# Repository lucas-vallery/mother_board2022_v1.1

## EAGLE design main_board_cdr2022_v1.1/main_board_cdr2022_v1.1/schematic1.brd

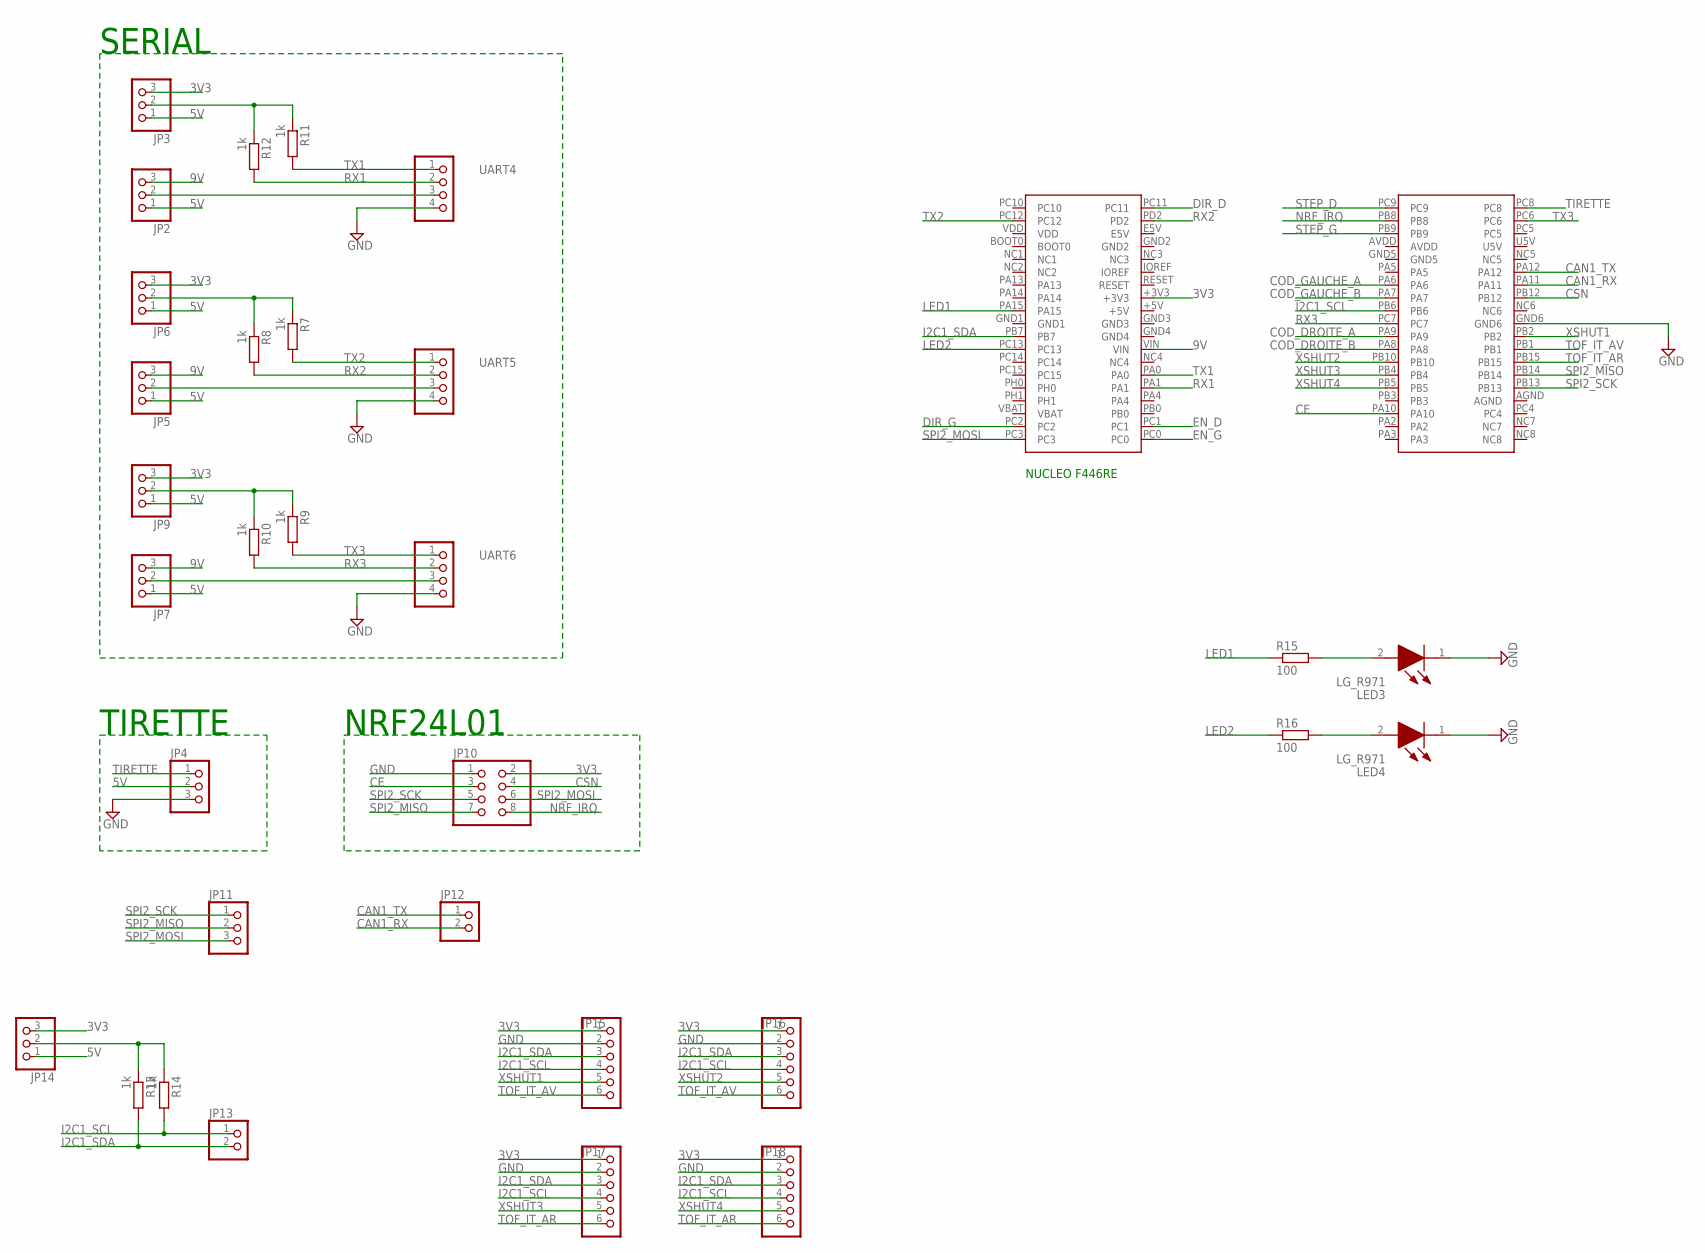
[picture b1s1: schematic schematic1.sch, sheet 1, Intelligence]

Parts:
JP2, JP3, JP4, JP5, JP6, JP7, JP9, JP11, JP14: PINHD-1X3; 1X03
JP10: PINHD-2X4; 2X04
JP12, JP13: PINHD-1X2; 1X02
JP15, JP16, JP17, JP18: PINHD-1X6; 1X06
LED3, LED4: LG_R971; LEDC2012X90N
R7, R8, R9, R10, R11, R12, R13, R14: 1k; R0805
R15, R16: 100; R0805
U$1: NUCLEO_F446RE; MB1136
UART4, UART5, UART6: PINHD-1X4; 1X04

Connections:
3V3: JP3.3, JP6.3, JP9.3, JP10.2, JP14.3, JP15.1, JP16.1, JP17.1, JP18.1, U$1.+3V3
5V: JP2.1, JP3.1, JP4.2, JP5.1, JP6.1, JP7.1, JP9.1, JP14.1; also elsewhere on the board
9V: JP2.3, JP5.3, JP7.3, U$1.VIN; also elsewhere on the board
CAN1_RX: JP12.2, U$1.PA11
CAN1_TX: JP12.1, U$1.PA12
CE: JP10.3, U$1.PA10
COD_DROITE_A: U$1.PA9; also elsewhere on the board
COD_DROITE_B: U$1.PA8; also elsewhere on the board
COD_GAUCHE_A: U$1.PA6; also elsewhere on the board
COD_GAUCHE_B: U$1.PA7; also elsewhere on the board
CSN: JP10.4, U$1.PB12
DIR_D: U$1.PC11; also elsewhere on the board
DIR_G: U$1.PC2; also elsewhere on the board
EN_D: U$1.PC1; also elsewhere on the board
EN_G: U$1.PC0; also elsewhere on the board
GND: JP4.3, JP10.1, JP15.2, JP16.2, JP17.2, JP18.2, LED3.1 (K), LED4.1 (K), U$1.GND6, UART4.4, UART5.4, UART6.4; also elsewhere on the board
I2C1_SCL: JP13.1, JP15.4, JP16.4, JP17.4, JP18.4, R14.2, U$1.PB6
I2C1_SDA: JP13.2, JP15.3, JP16.3, JP17.3, JP18.3, R13.2, U$1.PB7
LED1: R15.1, U$1.PA15
LED2: R16.1, U$1.PC13
unnamed: JP3.2, R11.1, R12.1
unnamed: JP6.2, R7.1, R8.1
unnamed: JP9.2, R9.1, R10.1
unnamed: LED3.2 (A), R15.2
unnamed: JP14.2, R13.1, R14.1
unnamed: LED4.2 (A), R16.2
NRF_IRQ: JP10.8, U$1.PB8
RX1: R12.2, U$1.PA1, UART4.2
RX2: R8.2, U$1.PD2, UART5.2
RX3: R10.2, U$1.PC7, UART6.2
SPI2_MISO: JP10.7, JP11.2, U$1.PB14
SPI2_MOSI: JP10.6, JP11.3, U$1.PC3
SPI2_SCK: JP10.5, JP11.1, U$1.PB13
STEP_D: U$1.PC9; also elsewhere on the board
STEP_G: U$1.PB9; also elsewhere on the board
TIRETTE: JP4.1, U$1.PC8
TOF_IT_AR: JP17.6, JP18.6, U$1.PB15
TOF_IT_AV: JP15.6, JP16.6, U$1.PB1
TX1: R11.2, U$1.PA0, UART4.1
TX2: R7.2, U$1.PC12, UART5.1
TX3: R9.2, U$1.PC6, UART6.1
VIN: JP2.2, UART4.3
VIN1: JP5.2, UART5.3
VIN2: JP7.2, UART6.3
XSHUT1: JP15.5, U$1.PB2
XSHUT2: JP16.5, U$1.PB10
XSHUT3: JP17.5, U$1.PB4
XSHUT4: JP18.5, U$1.PB5

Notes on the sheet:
NUCLEO F446RE
SERIAL
TIRETTE
NRF24L01

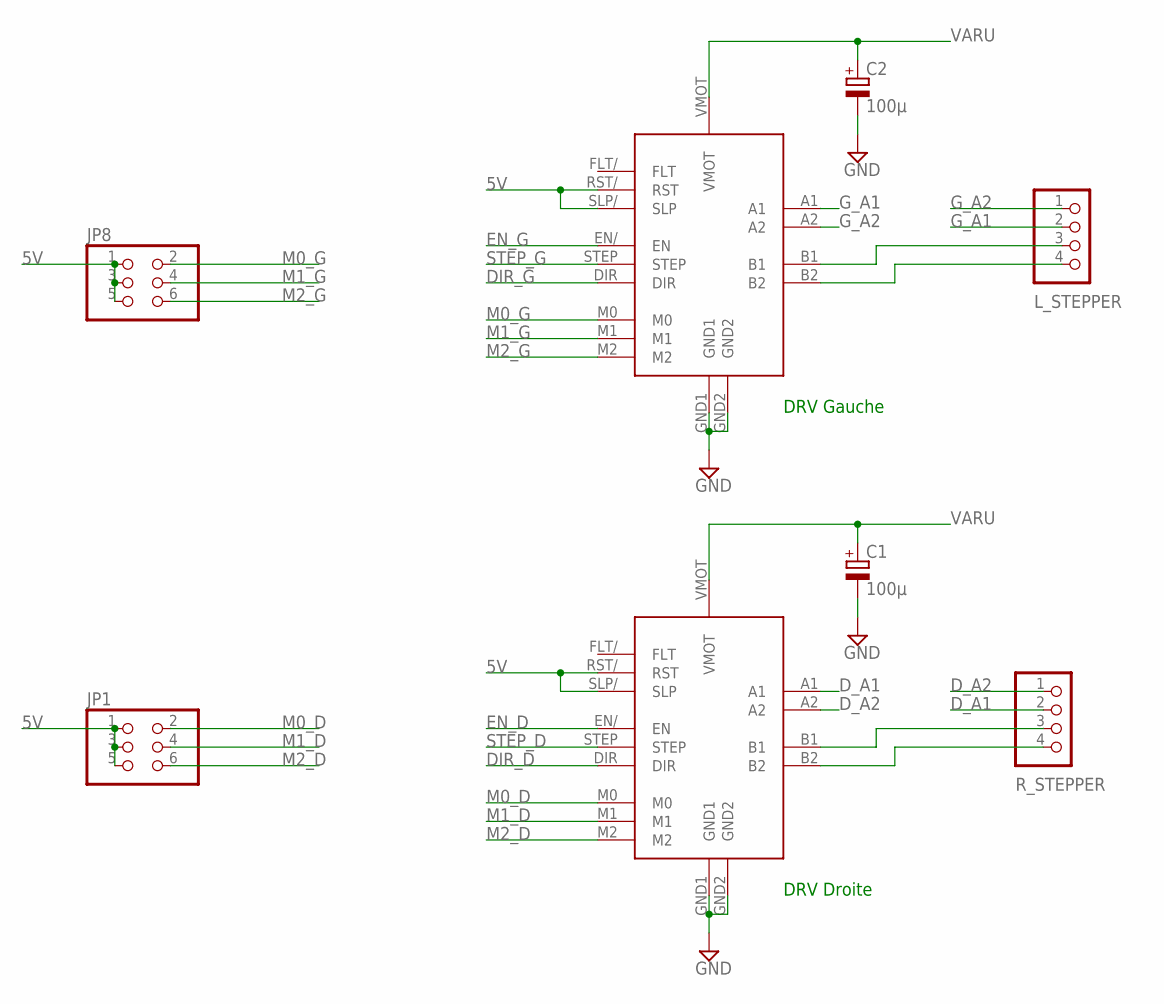
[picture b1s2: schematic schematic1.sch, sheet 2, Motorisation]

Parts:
C1, C2: 100µ; E5-6
JP1, JP8: PINHD-2X3; 2X03
L_STEPPER: PINHD-1X4; 1X04
R_STEPPER: PINHD-1X4; 1X04
U$2, U$3: POLOLU_DRV8825

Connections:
5V: JP1.1, JP1.3, JP1.5, JP8.1, JP8.3, JP8.5, U$2.RST/ (RST), U$2.SLP/ (SLP), U$3.RST/ (RST), U$3.SLP/ (SLP); also elsewhere on the board
DIR_D: U$3.DIR; also elsewhere on the board
DIR_G: U$2.DIR; also elsewhere on the board
D_A1: R_STEPPER.2, U$3.A1
D_A2: R_STEPPER.1, U$3.A2
EN_D: U$3.EN/ (EN); also elsewhere on the board
EN_G: U$2.EN/ (EN); also elsewhere on the board
GND: C1.-, C2.-, U$2.GND1, U$2.GND2, U$3.GND1, U$3.GND2; also elsewhere on the board
G_A1: L_STEPPER.2, U$2.A1
G_A2: L_STEPPER.1, U$2.A2
M0_D: JP1.2, U$3.M0
M0_G: JP8.2, U$2.M0
M1_D: JP1.4, U$3.M1
M1_G: JP8.4, U$2.M1
M2_D: JP1.6, U$3.M2
M2_G: JP8.6, U$2.M2
unnamed: L_STEPPER.3, U$2.B1
unnamed: L_STEPPER.4, U$2.B2
unnamed: R_STEPPER.3, U$3.B1
unnamed: R_STEPPER.4, U$3.B2
STEP_D: U$3.STEP; also elsewhere on the board
STEP_G: U$2.STEP; also elsewhere on the board
VARU: C1.+, C2.+, U$2.VMOT, U$3.VMOT; also elsewhere on the board

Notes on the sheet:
DRV Gauche
DRV Droite

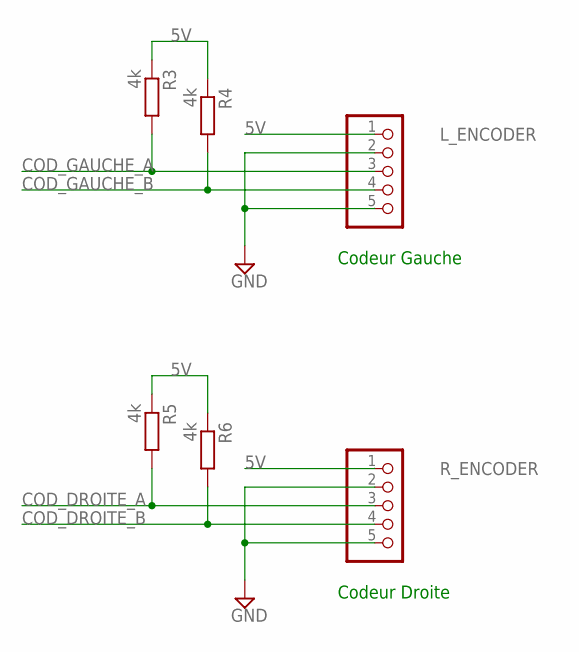
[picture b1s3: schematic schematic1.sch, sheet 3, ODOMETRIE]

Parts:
L_ENCODER: PINHD-1X5; 1X05
R3, R4, R5, R6: 4k; R0805
R_ENCODER: PINHD-1X5; 1X05

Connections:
5V: L_ENCODER.1, R3.1, R4.1, R5.1, R6.1, R_ENCODER.1; also elsewhere on the board
COD_DROITE_A: R5.2, R_ENCODER.3; also elsewhere on the board
COD_DROITE_B: R6.2, R_ENCODER.4; also elsewhere on the board
COD_GAUCHE_A: L_ENCODER.3, R3.2; also elsewhere on the board
COD_GAUCHE_B: L_ENCODER.4, R4.2; also elsewhere on the board
GND: L_ENCODER.2, L_ENCODER.5, R_ENCODER.2, R_ENCODER.5; also elsewhere on the board

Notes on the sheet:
Codeur Gauche
Codeur Droite

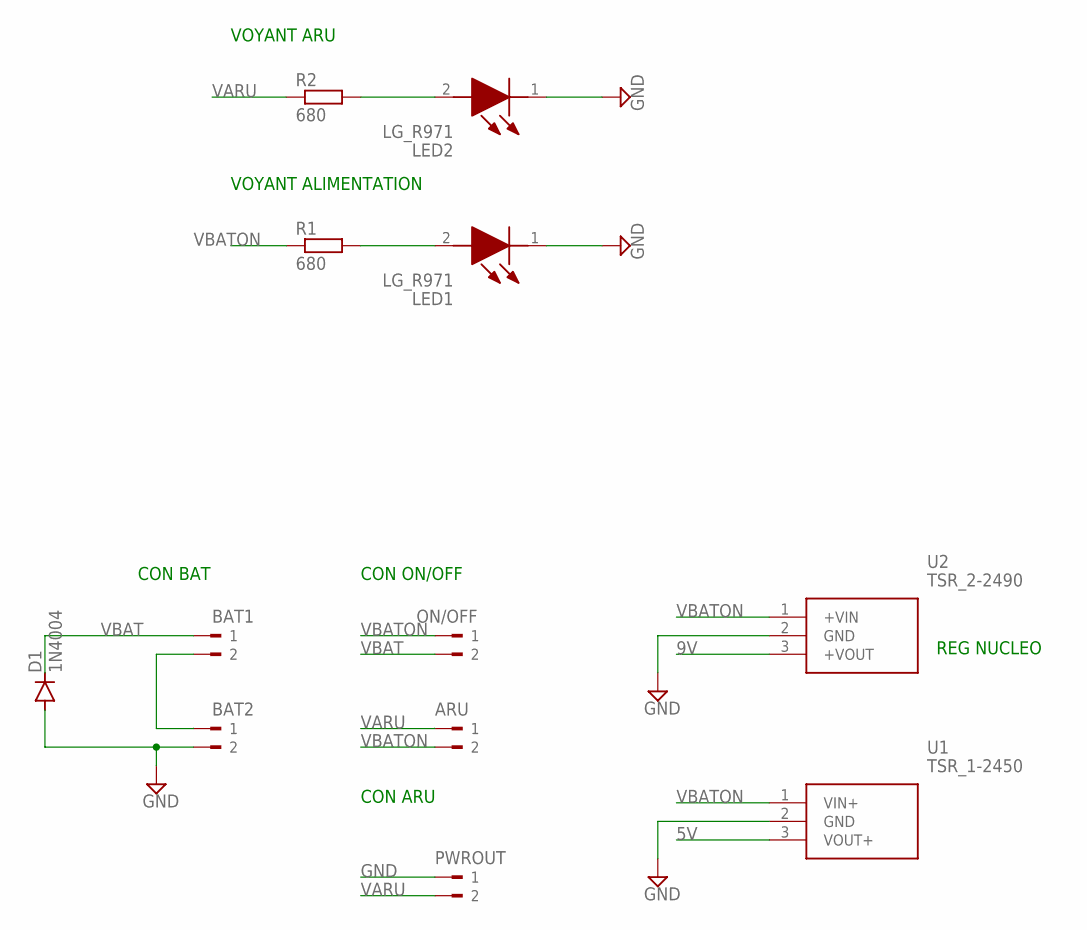
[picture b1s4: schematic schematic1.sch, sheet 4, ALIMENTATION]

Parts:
ARU: 180G-2
BAT1, BAT2: 180G-2
D1: 1N4004; DO41-10
LED1, LED2: LG_R971; LEDC2012X90N
ON/OFF: 180G-2
PWROUT: 180G-2
R1, R2: 680; R0805
U1: TSR_1-2450; TSR-1-24120
U2: TSR_2-2490; TSR_2-24XX

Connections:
5V: U1.3 (VOUT+); also elsewhere on the board
9V: U2.3 (+VOUT); also elsewhere on the board
GND: BAT2.2, D1.A, LED1.1 (K), LED2.1 (K), PWROUT.1, U1.2 (GND), U2.2 (GND); also elsewhere on the board
unnamed: LED1.2 (A), R1.2
unnamed: LED2.2 (A), R2.2
unnamed: BAT1.2, BAT2.1
VARU: ARU.1, PWROUT.2, R2.1; also elsewhere on the board
VBAT: BAT1.1, D1.C, ON/OFF.2
VBATON: ARU.2, ON/OFF.1, R1.1, U1.1 (VIN+), U2.1 (+VIN)

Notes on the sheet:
CON BAT
CON ON/OFF
CON ARU
REG NUCLEO
VOYANT ALIMENTATION
VOYANT ARU

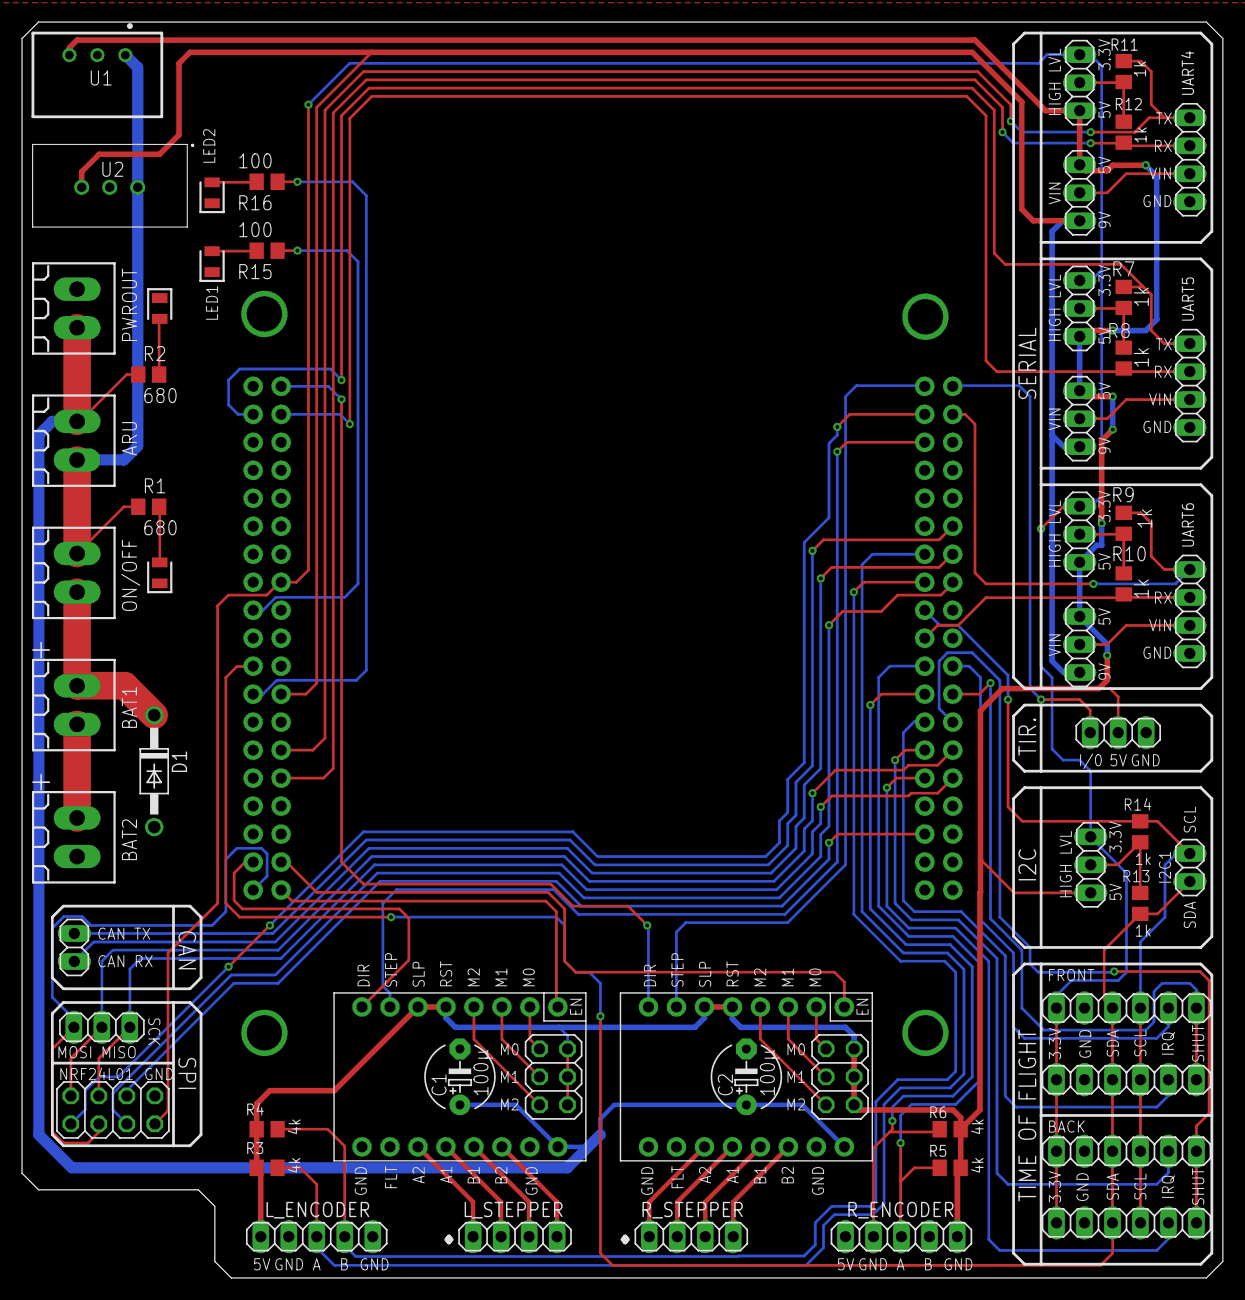
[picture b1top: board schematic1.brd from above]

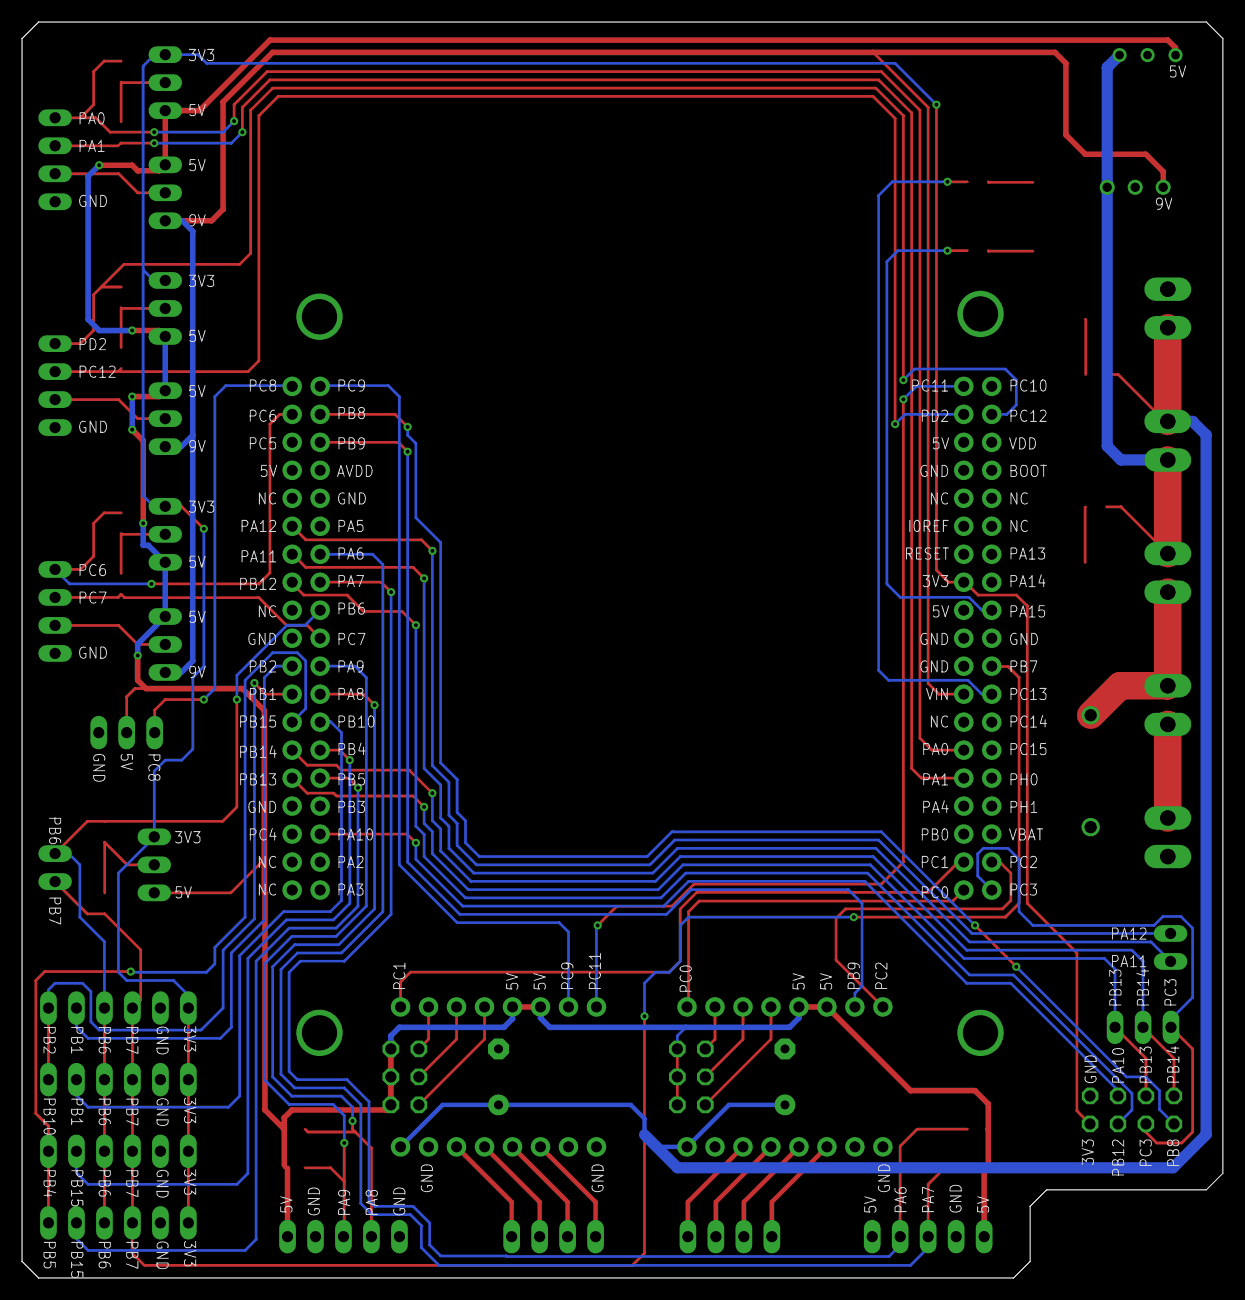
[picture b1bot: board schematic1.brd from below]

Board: 2 copper layers, 109.0 x 114.0 mm, 58 parts (2 on the bottom side), 68 nets.
